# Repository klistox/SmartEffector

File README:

Smart Effector fork with some dimensions modification to fit in the Pulpomaker
delta printer.

1) Distance between balls is 60mm
2) Balls has been moved out 5mm from its original place.
3) Balls holes converted to 4mm.
4) Lateral central holes added for spring wraping.
5) Pulpomaker Logo added.

Now 10mm balls can be used!

Thanks to www.duet3d.com!

See https://www.duet3d.com/DeltaSmartEffector for more information and to purchase a smart effector.

Duet3d Delta Smart Effector
Design by Tony Lock and David Crocker
LICENSE: see the LICENSE file in the repository
Documentation: https://duet3d.dozuki.com/Wiki/Smart_effector_and_carriage_adapters_for_delta_printer
Discussion: https://www.duet3d.com/forum/

Developed in KiCAD: http://www.kicad-pcb.org/display/KICAD/KiCad+EDA+Software+Suite

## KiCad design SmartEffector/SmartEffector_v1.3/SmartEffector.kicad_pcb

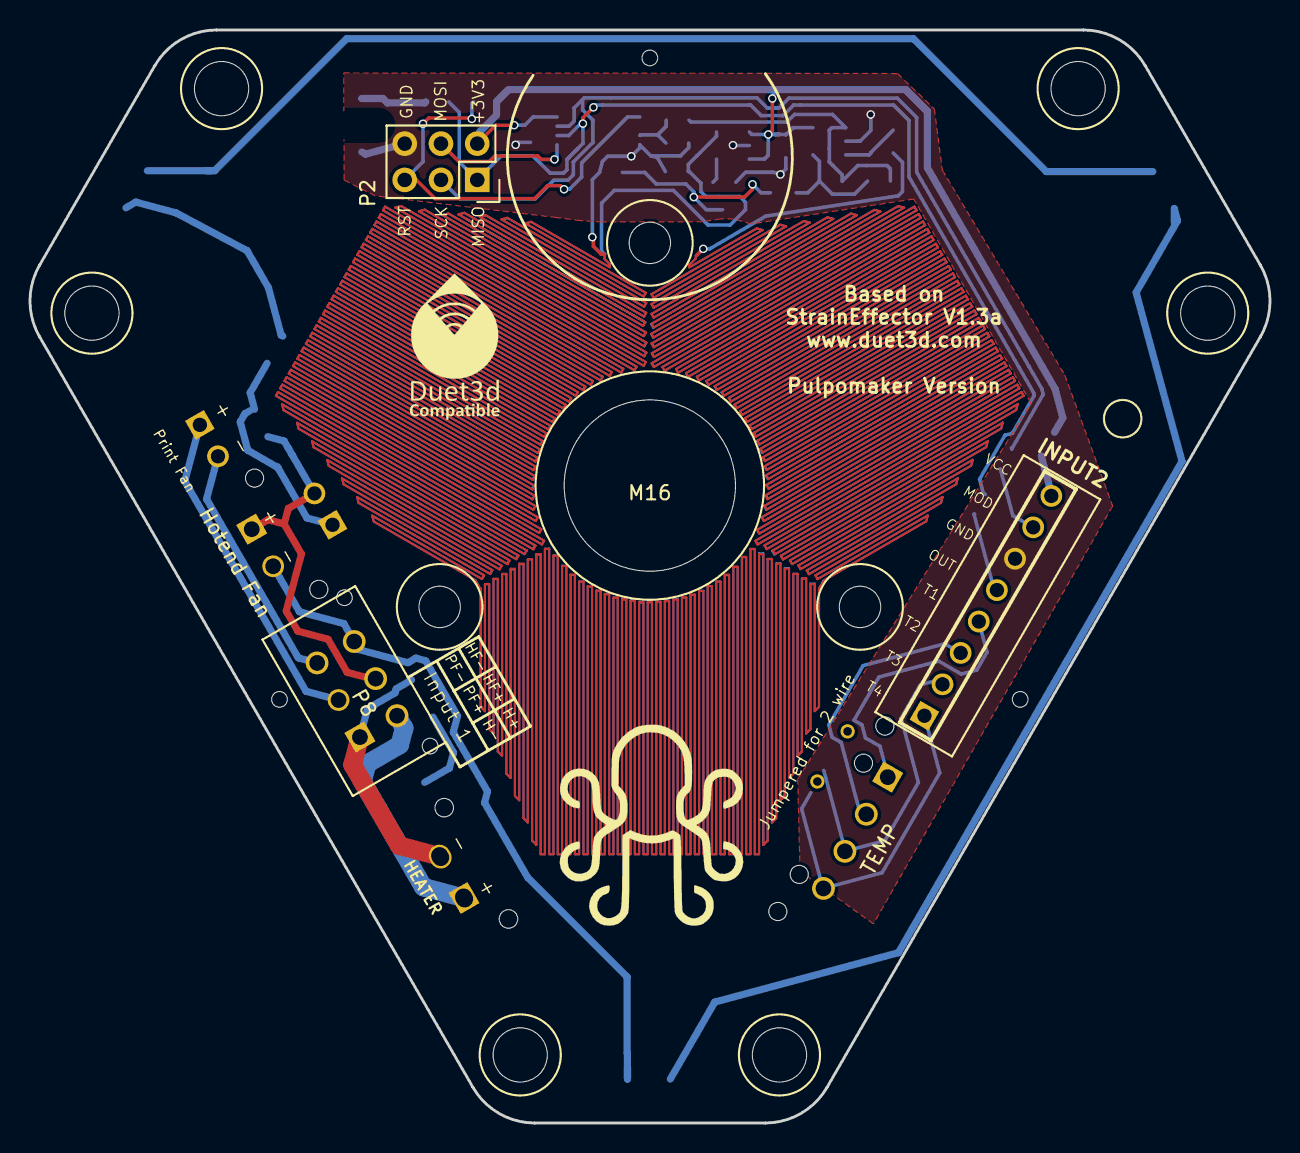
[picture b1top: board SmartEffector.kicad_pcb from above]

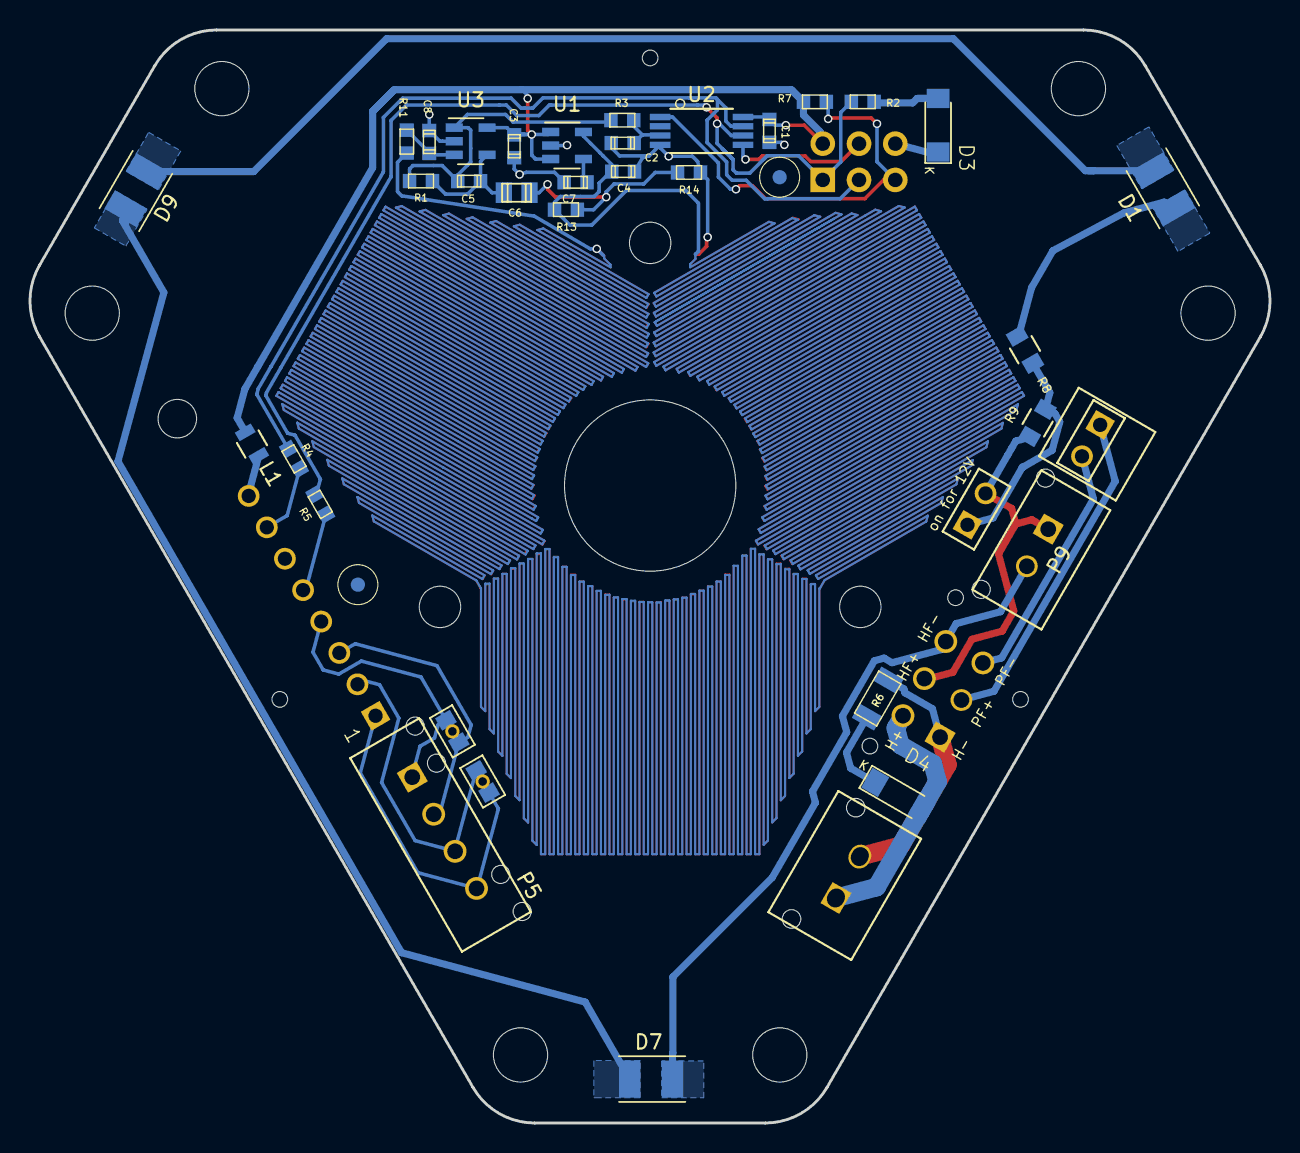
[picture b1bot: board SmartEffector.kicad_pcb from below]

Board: 2 copper layers, 86.9 x 76.6 mm, 57 parts (38 on the bottom side), 31 nets.

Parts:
C1: 100n; C_0603
C2, C7, C8: 10n; C_0603
C3, C4: 1u; C_0603
C5: 47p; C_0603
C6: 22u_<20%; C_0805
D1, D7, D9: Comms; LED_PLCC-2
D3: Comms; LED_1206_bottom_entry_v2
D4: Heat; LED_1206_bottom_entry_v2
G99: LOGO
JP1: Jumpered for 2 Wire; SJ_Bridged
JP2: Solder Jumper; SJ_Bridged
JP3: on for 12V; JUMPER
L1: 22uH; R_0805
M1, M2: FID; Fiducial_1mm_Dia_2.54mm_Outer_CopperTop
M3, M4, M5, M6, M7, M8: M_3.8mm; M4_3.8
M9, M10, M11: M_2.9mm; MountingHole_2.9mm
M13: Ziptie; Ziptie_small
M15: OSHW_Logo; LOGO_Duet3dCompatible
M16: 12mm; 12mmHole
M97, M98, M99: M2_1.4mm; M2_2.4
P2: PROG; Socket_Strip_Straight_2x03
P3: INPUT2; PIN_ARRAY_8x1
P4: HEATER; Minifit3.0+screwterm3.5MM_2X1
P5: TEMP; Microfit_01x02or04_43650-0227
P7: Print Fan; PIN_ARRAY_2X1
P8: Input 1; Microfit_02x03
P9: Hotend Fan; Microfit_01x02_43650-0227
R1: 10M; R_0603
R2: 150R; R_0603
R3, R4, R7, R11: 5K1; R_0603
R5: 1K0; R_0603
R6: 1K5_0.5W+; R_1206
R8: 140R_0.33W+; R_0805_extended_pads
R9: 604R_0.33W+; R_0805_extended_pads
R13, R14: 10K_1%; R_0603
U1: LDK130M08; SOT-23-5L
U2: ATTINY45; TSSOP-8_3x4.4mm_Pitch0.65mm
U3: MCP6286; SOT-23-5L

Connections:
+3V3: C1.1, C3.1, L1.2, P2.2, R7.2, U1.1, U1.3, U2.8, U3.5
ADC2: C2.1, R3.2, U2.3
B: C1.2, C2.2, C3.2, C4.1, C4.2, C7.1, C8.2, D3.1, P2.6, P3.6, R11.1, R13.1, R14.2, U1.2, U1.5, U2.4, U3.2
H_Fan_+: JP3.2, P8.5, P9.1, R9.1
H_Fan_-: D7.1, P8.6, P9.2
Heater+: D4.2, P4.1, P8.4
Heater-: P4.2, P8.1, R6.2
MISO: P2.1, R2.2, R5.2, U2.6
MOSI: P2.4, U2.5
unnamed: C5.1, R1.2, R3.1, U3.1
unnamed: C5.2, C6.1, R1.1, U3.4
unnamed: C6.2, R13.2, R14.1
unnamed: C7.2, U1.4
unnamed: C8.1, R11.2, U3.3
unnamed: D1.1, D9.2
unnamed: D1.2, R8.2
unnamed: D3.2, R2.1
unnamed: D4.1, R6.1
unnamed: D7.2, D9.1
unnamed: JP3.1, R8.1, R9.2
unnamed: L1.1, P3.8
unnamed: P3.5, R5.1
unnamed: P3.7, R4.1
P_Fan_+: P7.1, P8.2
P_Fan_-: P7.2, P8.3
RST: P2.5, R7.1, U2.1
SCK: P2.3, R4.2, U2.7
Therm1: JP1.1, P3.4, P5.1
Therm2: JP1.2, P3.3, P5.2
Therm3: JP2.1, P3.2, P5.3
Therm4: JP2.2, P3.1, P5.4

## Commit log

2018-09-13 Added modifications for puplomaker delta printer
2018-09-13 charlio modification, gerbers and autogenerated BOM list
2018-09-13 Readme typo corrected
2018-11-26 Error in README definition
